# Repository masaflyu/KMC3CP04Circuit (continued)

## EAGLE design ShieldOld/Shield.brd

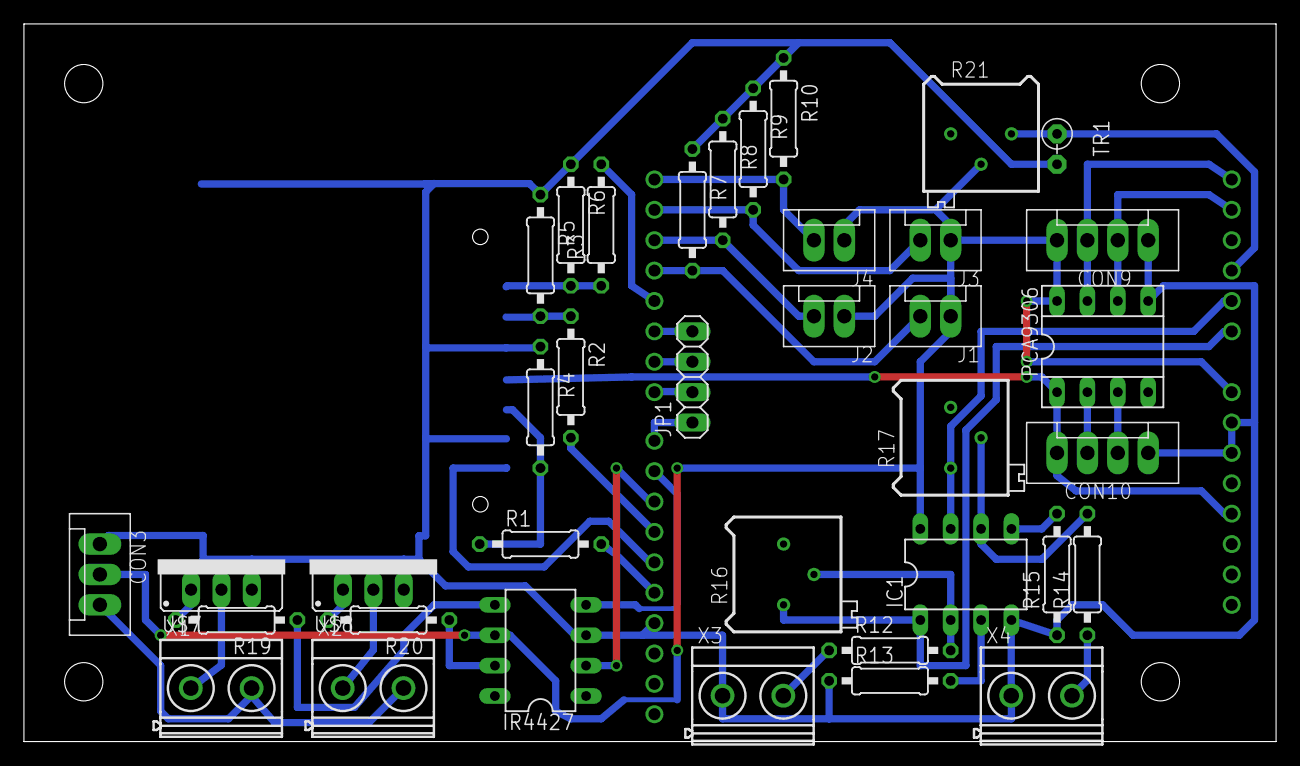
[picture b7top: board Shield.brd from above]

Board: 2 copper layers, 104.7 x 60.0 mm, 39 parts (1 on the bottom side), 40 nets.

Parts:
CON1: DM1A-DSF-PEJ
CON3: CON3
CON9, CON10: CON4
IC1: AD712N; DIL08
IR4427: DIL08
J1, J2, J3, J4: CON2
JP1: 1X04
PCA9306: SOCKET-08
R1, R2, R3: 470; 1/4W-H4_(0207/10)
R4, R5, R6: 1k; 1/4W-H4_(0207/10)
R7, R8, R9, R10: 10k; 1/4W-H4_(0207/10)
R12, R13, R14, R15: 100; 1/4W-H4_(0207/10)
R16, R17: 100k; RTRIM64P
R19, R20: 220?; 1/4W-H4_(0207/10)
R21: 10k; RTRIM64P
TR1: 10k(25C); RS-2,5
U$1: ARDUINO-IOPIN; ARDUINO-SHIELD-PIN-ONLY
U$7, U$8: TO-220(MOS-FET_N); TO-220
X1, X2, X3, X4: MKDSN1,5/2-5,08

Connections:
+3.3V: CON1.4, CON10.P$1, PCA9306.1, U$1.3.3V
+5V: CON3.P$2, CON9.P$1, IC1.8, IR4427.6, J1.P$2, J2.P$2, J3.P$2, J4.P$2, PCA9306.8, R21.2, U$1.VIN
+9V: CON3.P$1, X1.2, X2.2
DGND: CON1.3, CON1.6, CON1.GND1, CON1.GND2, CON1.GND3, CON1.GND4, CON3.P$3, CON9.P$4, CON10.P$4, IC1.4, IR4427.3, PCA9306.5, R4.1, R5.1, R6.1, R7.1, R8.1, R9.1, R10.1, R13.1, R15.1, TR1.2, U$1.GND@1, U$1.GND@2, U$1.GND@3, U$7.3, U$8.3, X3.1, X4.1
unnamed: CON1.2, R2.1, R5.2
unnamed: R1.2, U$1.D13
unnamed: CON1.5, R1.1, R4.2
unnamed: J1.P$1, R7.2, U$1.D3
unnamed: R2.2, U$1.D11
unnamed: CON1.1, R3.1, R6.2
unnamed: R3.2, U$1.D4
unnamed: J2.P$1, R8.2, U$1.D2
unnamed: CON1.7, U$1.D12
unnamed: J3.P$1, R9.2, U$1.D1
unnamed: J4.P$1, R10.2, U$1.D0
unnamed: CON10.P$2, PCA9306.2
unnamed: CON9.P$3, PCA9306.6, U$1.A4
unnamed: CON9.P$2, PCA9306.7, U$1.A5
unnamed: CON10.P$3, PCA9306.3
unnamed: IC1.2, R12.2, R16.2
unnamed: IC1.3, R13.2
unnamed: IC1.5, R15.2
unnamed: IC1.6, R14.2, R17.2
unnamed: IC1.1, R16.1, U$1.A0
unnamed: IC1.7, R17.1, U$1.A1
unnamed: JP1.4, U$1.D5
unnamed: JP1.3, U$1.D6
unnamed: JP1.2, U$1.D7
unnamed: JP1.1, U$1.D8
unnamed: U$7.2, X1.1
unnamed: R19.2, U$7.1
unnamed: R21.3, TR1.1, U$1.A2
unnamed: IR4427.2, U$1.D10
unnamed: IR4427.4, U$1.D9
unnamed: U$8.2, X2.1
unnamed: R20.2, U$8.1
unnamed: IR4427.5, R19.1
unnamed: IR4427.7, R20.1
unnamed: R14.1, X4.2
unnamed: R12.1, X3.2
